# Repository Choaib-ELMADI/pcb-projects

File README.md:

# PCB Projects

The `pcb-projects` repository features a variety of electronic PCB designs for hobbyists and enthusiasts. Each project includes schematics, PCB layouts, and images to make it easy to explore and replicate. The repository also contains a folder for notes, offering tips and useful information for both **Altium Designer** and **KiCad**, as well as custom hardware libraries for **KiCad**.

<div align="center">

</div>

## 🟤 Altium Designer

A growing collection of PCB projects created using **Altium Designer**:

#### [1. LiPo Battery Charger:](./Altium%20Designer/LiPo%20Battery%20Charger/)

<div align="center">

</div>

#### [2. IR Module:](./Altium%20Designer/IR%20Module/)

<div align="center">

</div>

#### [3. Sequential LEDs:](./Altium%20Designer/Sequential%20LEDs/)

<div align="center">

</div>

#### [4. LED Chaser:](./Altium%20Designer/LED%20Chaser/)

<div align="center">

</div>

#### [5. Custom TP4056 Module - SMD Version:](./Altium%20Designer/Custom%20TP4056%20Module%20-%20SMD/)

<div align="center">

</div>

#### [6. Custom TP4056 Module - THD Version:](./Altium%20Designer/Custom%20TP4056%20Module%20-%20THD/)

<div align="center">

</div>

## 🔵 KiCad

A growing collection of PCB projects designed using **KiCad**:

#### [1. Pulse Oximeter Medical Device:](./KiCad/Pulse%20Oximeter%20Medical%20Device/)

<div align="center">

</div>

## 📗 KiCad Libraries

A collection of custom hardware libraries for **KiCad** components that aren’t available by default. Each library includes symbols, footprints, and 3D models.

#### [1. 2.4'' 240x320 LCD Display TFT Module:](./Libraries/2.4''%20240x320%20LCD%20Display%20TFT%20Module/)

<div align="center">

</div>

Feel free to explore, suggest new projects, or open pull requests for libraries. Happy tinkering, and stay tuned for more updates!

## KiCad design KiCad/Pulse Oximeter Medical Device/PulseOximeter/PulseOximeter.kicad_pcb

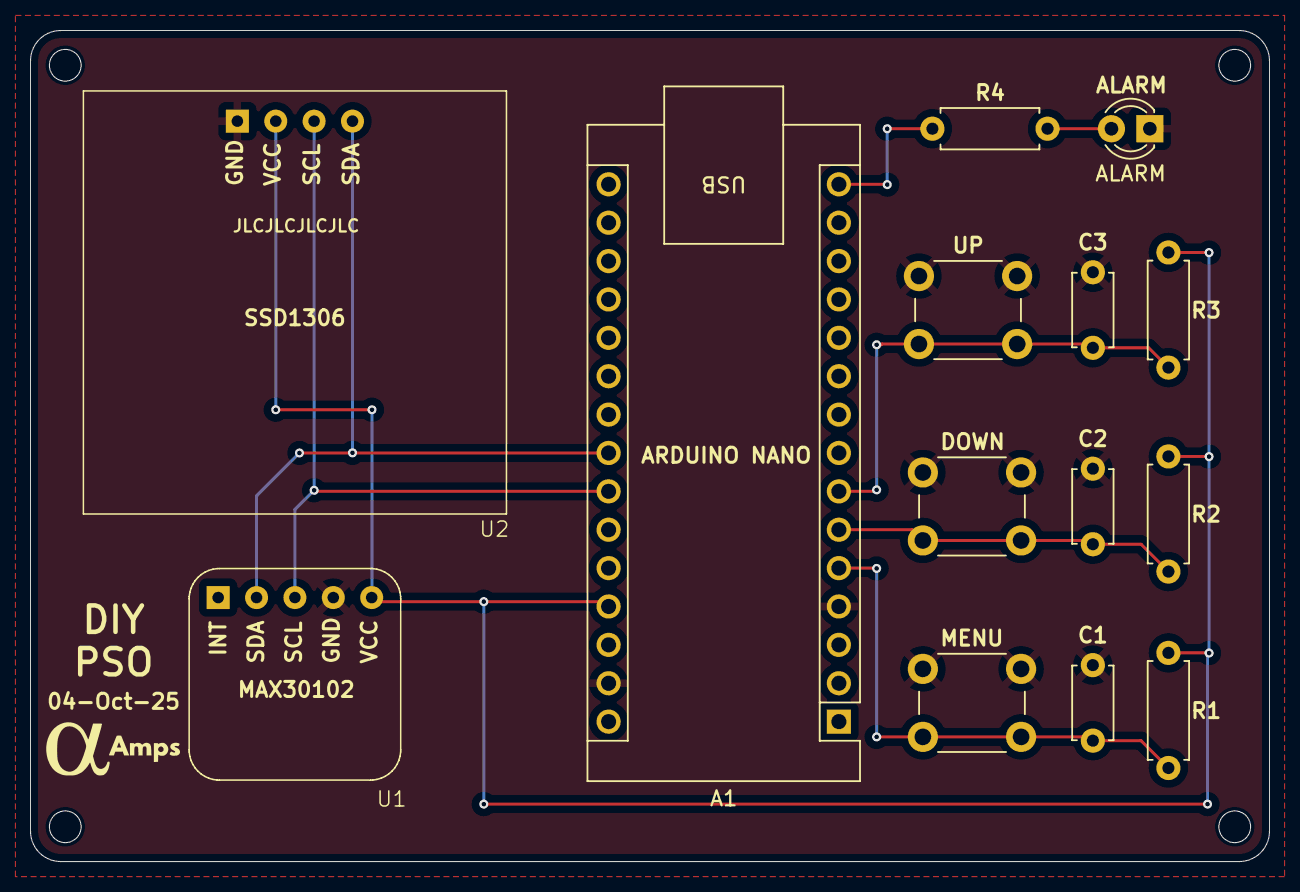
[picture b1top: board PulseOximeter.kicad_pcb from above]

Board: 4 copper layers, 82.0 x 55.0 mm, 14 parts (0 on the bottom side), 9 nets.

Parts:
A1: Arduino_Nano_v3.x; Arduino_Nano
ALARM: LED; LED_D3.0mm
C1, C2, C3: 100n; C_Disc_D4.7mm_W2.5mm_P5.00mm
DOWN: SW_Push; SW_PUSH_6mm
MENU: SW_Push; SW_PUSH_6mm
R1, R2, R3, R4: 1K; R_Axial_DIN0207_L6.3mm_D2.5mm_P7.62mm_Horizontal
U1: MAX30102; MAX30102_Module
U2: SSD1306; SSD1306_Module
UP: SW_Push; SW_PUSH_6mm

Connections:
+5V: A1.27 (+5V), R1.1, R2.1, R3.1, U1.5 (VCC), U2.2 (VCC)
GND: A1.4 (GND), A1.29 (GND), ALARM.1 (K), C1.2, C2.2, C3.2, DOWN.1, MENU.1, U1.4 (GND), U2.1 (GND), UP.1
unnamed: A1.23 (A4), U1.2 (SDA), U2.4 (SDA)
unnamed: A1.24 (A5), U1.3 (SCL), U2.3 (SCL)
unnamed: A1.5 (D2), C1.1, MENU.2, R1.2
unnamed: A1.6 (D3), C2.1, DOWN.2, R2.2
unnamed: A1.7 (D4), C3.1, R3.2, UP.2
unnamed: A1.15 (D12), R4.1
unnamed: ALARM.2 (A), R4.2

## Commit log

2024-02-05 Add first pcb project: LiPo Battery Charger
2024-02-06 Remove the first folder
2024-02-06 Add initial files for first pcb project
2024-02-06 Add all the necessary files and folders
2024-02-06 Add project images
2024-02-06 Rename folders
2024-03-29 Initialize a new pcb project 'Flashing LED'
2024-03-30 Rename the pcb project/files
2024-03-30 Create the pcb schematic and start build the pcb layout
2024-03-30 Update README.md file
2024-03-30 Add .gitignore files
2024-03-30 Resize projects images
2024-03-30 Add the pcb result images
2024-03-31 Route the pcb and Rename the project folder
2024-03-31 Complete the IR module pcb layout 2D/3D
2024-03-31 Update the IR module project images
2024-03-31 Update the Lipo Battery Charger project images
2024-03-31 Rename 2d-pcb.png to 2d-pcb.png
2024-03-31 Rename 3d-pcb.png to 3d-pcb.png
2024-03-31 Rename schematic.png to schematic.png
2024-06-07 Ignore the power regulator project
2024-06-07 Initialize a new pcb project
2024-06-07 Create/Wire the pcb schematic
2024-06-08 Add some notes
2024-06-08 Place the components on the pcb board
2024-06-08 Routing the traces
2024-06-13 Start routing the Sequential LEDs board
2024-06-13 Complete the Sequential LEDs board
2024-06-14 Generate fabrication files
2024-06-14 Polygons configuration
2024-06-14 Initiate the LED Chaser PCB project
2024-06-14 Create the schematic document
2024-06-14 Create/Route the pcb document
2024-06-15 Complete the LED Chaser board
2024-06-15 Add some docs
2024-06-15 Fix some design rule check errors
2024-06-15 Add pcb images/docs
2024-06-29 Video: Altium Designer - import libraries
2024-08-25 Update docs
2024-08-25 Update the IR module project
2024-08-25 Update the lipo battery charger project
2024-08-25 Update the sequential leds project
2024-08-25 Remove cached files
2024-08-26 Update the led chaser project
2024-08-26 Custom TP4056 charging module...
2024-08-27 Create the pcb schematic
2024-08-27 Create the SMD pcb document
2024-08-27 Troubleshooting...
2024-08-27 Fresh restart...
2024-08-27 Fix the routing issue
2024-08-27 Route the pcb document
2024-08-27 Update pcb document routing
2024-08-27 Complete the custom TP4056 module - SMD version
2024-08-27 Board shape design notes
2024-08-28 Update pcb images
2024-08-28 Update the pcb files
2024-08-28 Start the custom TP4056 module - THD version
2024-08-28 Complete the custom TP4056 module - THD version
2024-08-28 Add mounting holes to the custom TP4056 module
2024-08-28 Mounting holes docs
2024-12-17 Update Altium Designer notes
2024-12-27 Update .gitignore files
2024-12-27 Start new PCB projects with KiCad
2024-12-28 Update repo structure
2025-01-08 Add KiCad projects template
2025-01-08 Create a PCB schematics flat structure
2025-01-08 Update ESC project resources
2025-01-08 Create ESC block diagram
2025-01-10 Update MCU schematic file
2025-01-10 Update MCU schematic net labels
2025-01-19 Update MCU schematic
2025-01-19 Add voltage divider circuit to MCU schematic
2025-01-20 Create MOSFETs driver schematic
2025-01-20 Update MOSFETs driver schematic
2025-01-21 Add MOSFETs driver input ports
2025-01-21 Working with the JLC2KiCadLib library
2025-10-03 Create MOSFETs schematic (await ESC project)
2025-10-03 Create the pulse oximeter main schematic
2025-10-03 Assign footprints to symbols
2025-10-04 Create custom footprints for symbols
2025-10-04 Set PCB settings based on manufacturer
2025-10-04 Create PCB layout and check DRC
2025-10-04 Edit silkscreen text layer
2025-10-04 Add PCB mounting holes
2025-10-04 Generate gerbers fabrication files
2025-10-05 Add useful manufacturing templates for KiCad
2025-10-05 Add new KiCad PCB images
2025-10-07 Add the 2.4'' 240x320 LCD Display TFT Module KiCad library
2025-10-07 Update README.md file with libraries section
